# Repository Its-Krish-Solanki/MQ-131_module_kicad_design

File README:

MQ-131 sensor is used to detect ozone gas levels and also has sensitivity to strong oxides like CL2 and NO2

MQ-131 conuductivity reduces with increase in ozone gas concentration.
We can convert the change in conductivity to reading using an external analog to digital convertor
LM393 is used to light up an LED when the ozone concentration reached a certain level that level can be determined by the load resistor.
Over here i used a 10k resistor, the led will turn on when ozone concentration reaches 500 ppb(parts per billion) 

Schematic

Layout

3D viewer

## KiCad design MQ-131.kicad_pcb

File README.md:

MQ-131 sensor is used to detect ozone gas levels and also has sensitivity to strong oxides like CL2 and NO2

MQ-131 conuductivity reduces with increase in ozone gas concentration.
We can convert the change in conductivity to reading using an external analog to digital convertor
LM393 is used to light up an LED when the ozone concentration reached a certain level that level can be determined by the load resistor.
Over here i used a 10k resistor, the led will turn on when ozone concentration reaches 500 ppb(parts per billion) 

Schematic

Layout

3D viewer

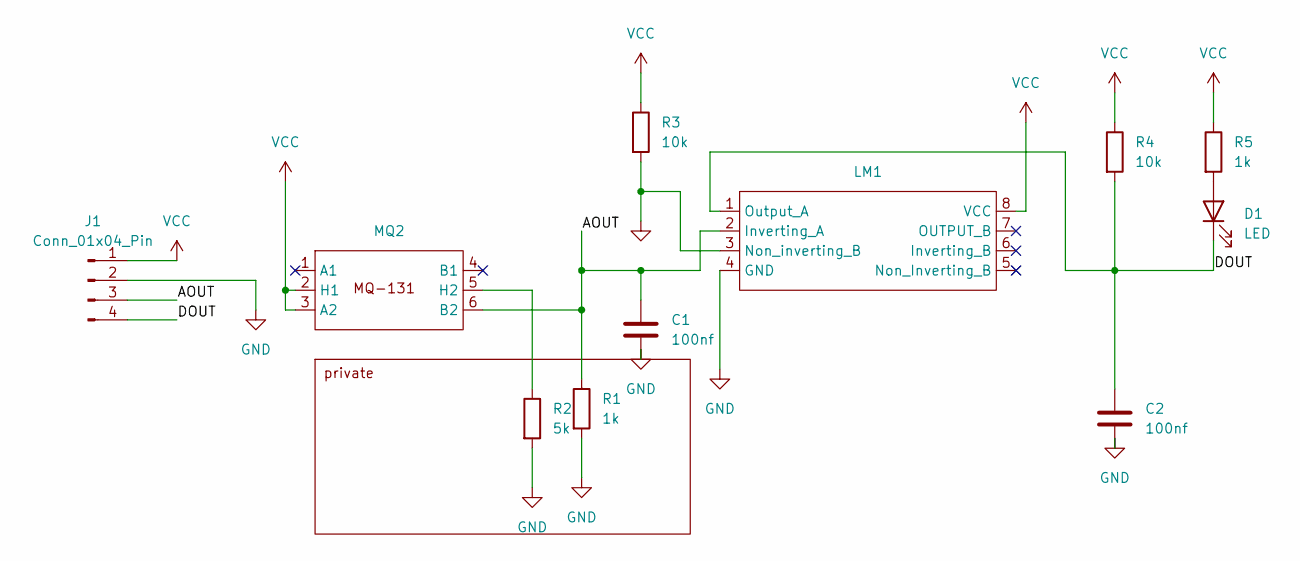
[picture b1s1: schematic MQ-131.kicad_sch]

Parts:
C1, C2: 100nf; C_Radial_D4.0mm_H7.0mm_P1.50mm
D1: LED; LED_D3.0mm
J1: Conn_01x04_Pin; NS-Tech_Grove_1x04_P2mm_Vertical
LM1: DIP-8_W7.62mm
MQ2: MQ-131
R1, R5: 1k; R_Axial_DIN0204_L3.6mm_D1.6mm_P7.62mm_Horizontal
R2: 5k; R_Axial_DIN0204_L3.6mm_D1.6mm_P7.62mm_Horizontal
R3, R4: 10k; R_Axial_DIN0204_L3.6mm_D1.6mm_P7.62mm_Horizontal

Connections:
/AOUT: C1.1, J1.3, LM1.2 (Inverting_A), MQ2.6 (B2), R1.1
/DOUT: C2.1, D1.1 (K), J1.4, LM1.1 (Output_A), R4.2
GND: C1.2, C2.2, J1.2, LM1.3 (Non_inverting_B), LM1.4 (GND), R1.2, R2.2, R3.2
unnamed: D1.2 (A), R5.2
unnamed: MQ2.5 (H2), R2.1
VCC: J1.1, LM1.8 (VCC), MQ2.2 (H1), MQ2.3 (A2), R3.1, R4.1, R5.1

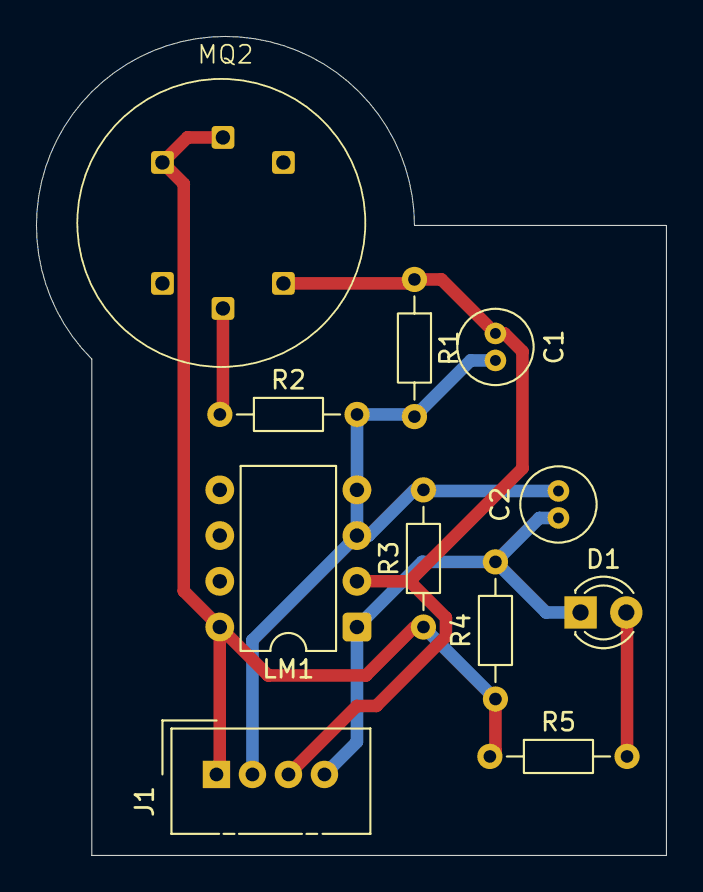
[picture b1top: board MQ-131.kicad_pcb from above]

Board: 2 copper layers, 35.0 x 45.5 mm, 11 parts (0 on the bottom side), 6 nets.
